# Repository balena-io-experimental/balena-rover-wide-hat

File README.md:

# Resin Rover Wide-HAT

This board is a full-fledged rover in a wide HAT form factor, which mean it covers an entire Raspberry Pi 3.

The motors are driven by two [DRV8830](www.ti.com/product/drv8830) I²C motor controllers, one for the left wheels and the other for the right wheels. The slave I²C address for the left wheels driver are ``0xC0h`` and ``0xC1h``, for write and read respectively. As for the right wheels driver, they are ``0xD0h`` and ``0xD1h``, respectively.

Currently the maximum current for each motor is 500mA.

The line following circuit is made from three reflective sensors, which are read by an [ADC](http://www.ti.com/product/ADS1015) at address ``0x48h``. The left, center and right sensors are read at analog inputs ``AIN0``, ``AIN1`` and ``AIN2`` respectively.

It supports a 2-cell LiPo battery with an on-board charger which should be supplied through a DC barrel jack connector from 9V to 12V, at 1A.

The only manufacturing constrain of this board is that it needs 2oz or higher copper weight.

Besides the components listed on the BoM, the rest of the parts needed are:

* 4 x Micro Metal Gearmotor ([example](https://shop.pimoroni.com/products/micro-metal-gearmotor-extended-back-shaft))
* 4 x Micro Metal Gearmotor Bracket ([example](https://shop.pimoroni.com/products/pimoroni-gearmotor-bracket-pair))
* 4 x Wheels ([example](https://shop.pimoroni.com/products/pololu-wheel-32x7mm-pair))
* 1 x 2-cell LiPo battery with JST-XH connector ([example](https://hobbyking.com/en_us/turnigy-5000mah-2s-20c-lipo-pack.html))

Raspberry Pi mounting holes were taken from [here](https://github.com/xesscorp/RPi_Hat.pretty/blob/master/RPi_Hat_Mounting_Hole.kicad_mod) and inductor footprint from [here](https://github.com/Tinkerforge/kicad-libraries/blob/master/SRN6045.kicad_mod).

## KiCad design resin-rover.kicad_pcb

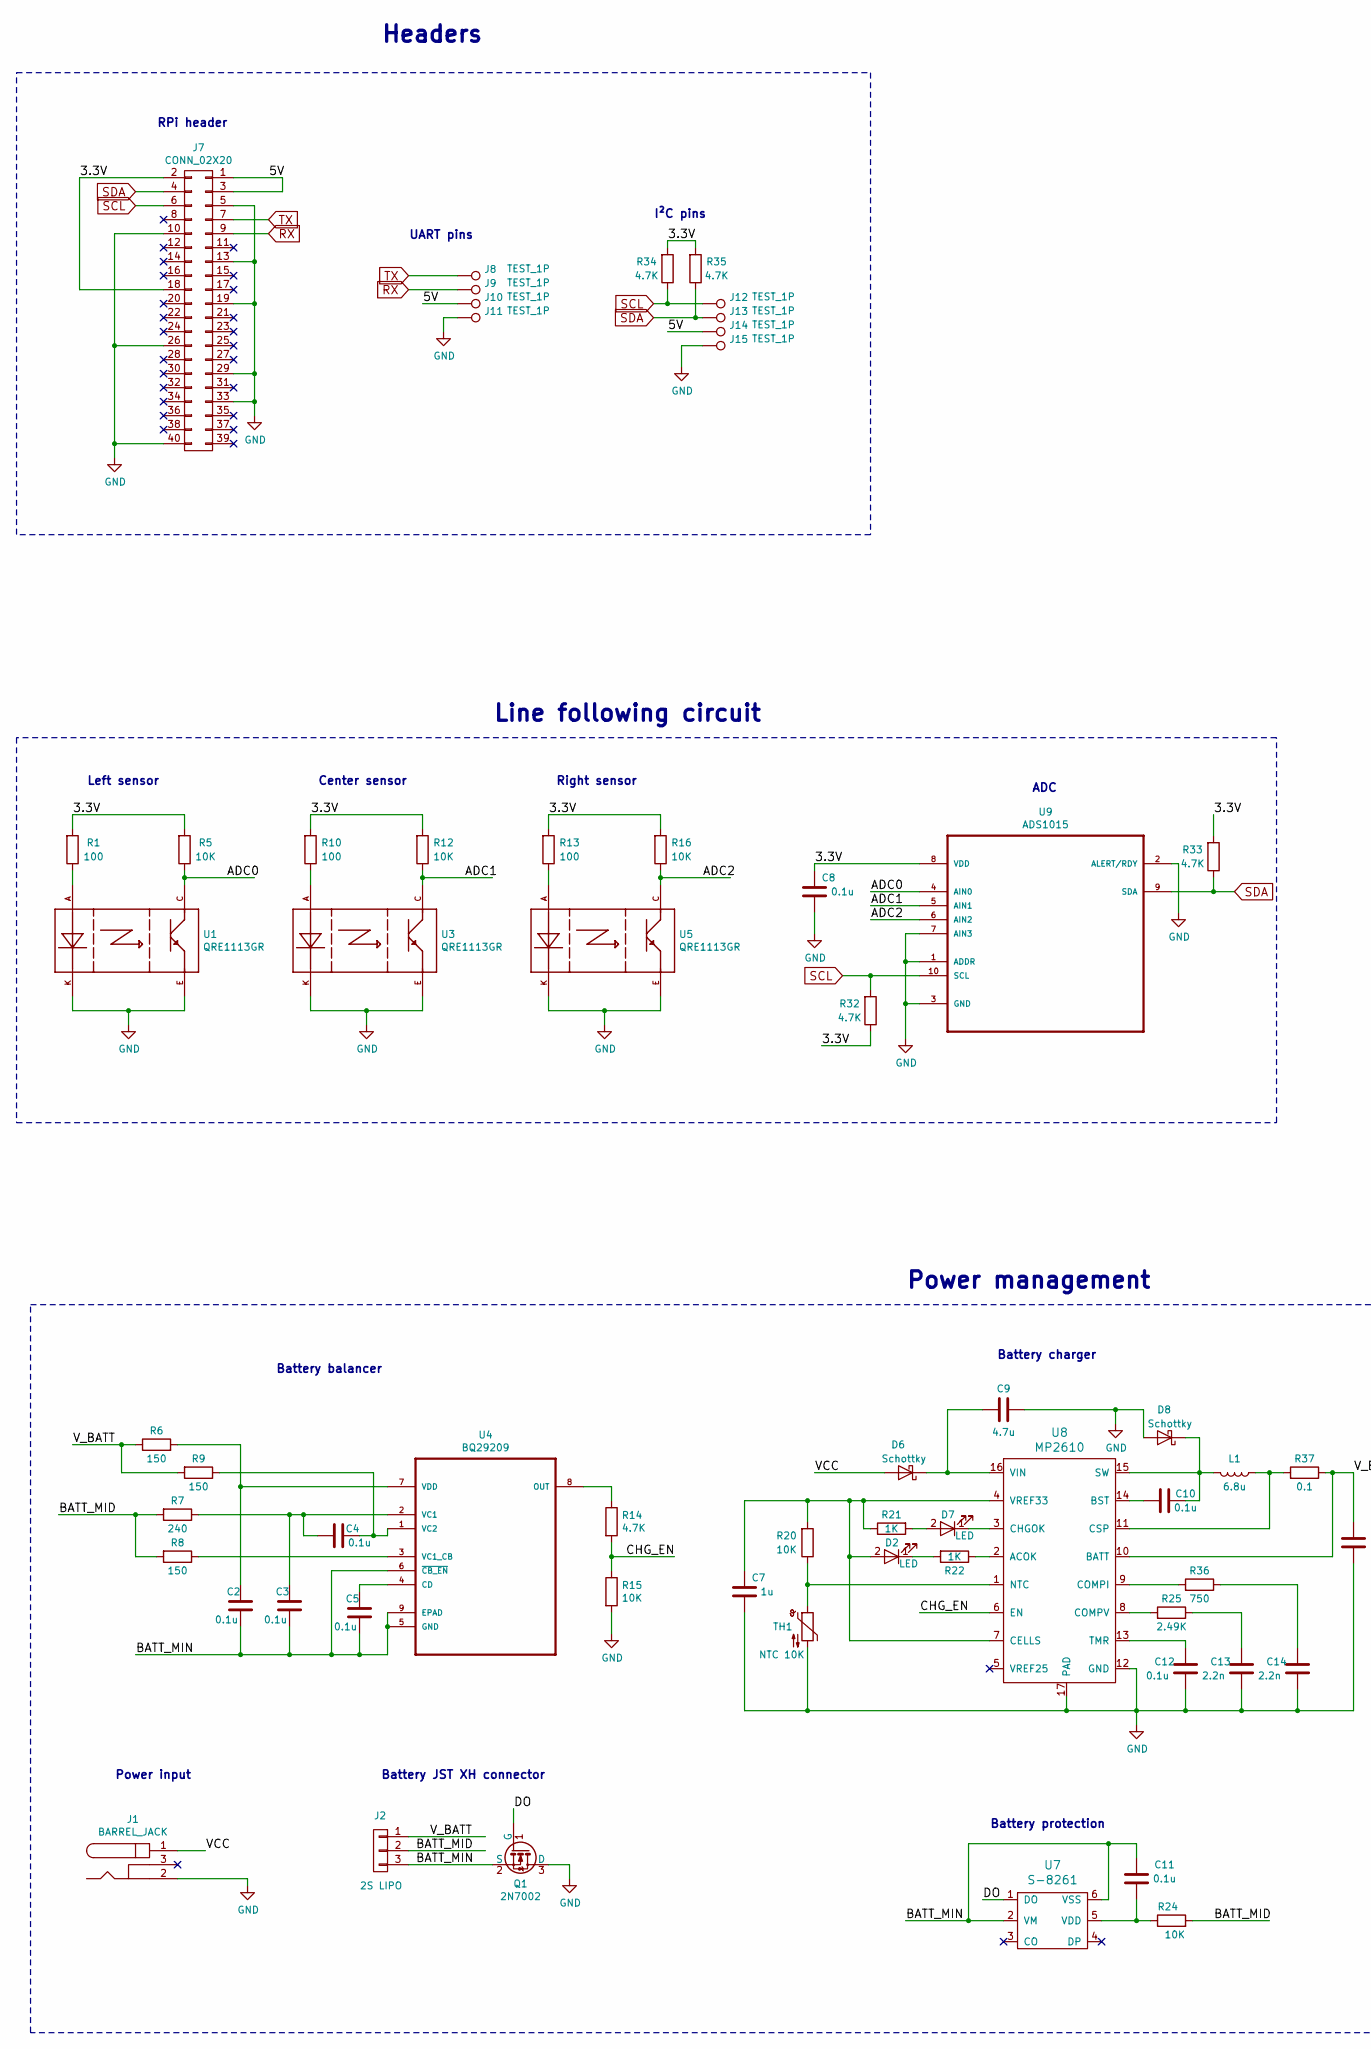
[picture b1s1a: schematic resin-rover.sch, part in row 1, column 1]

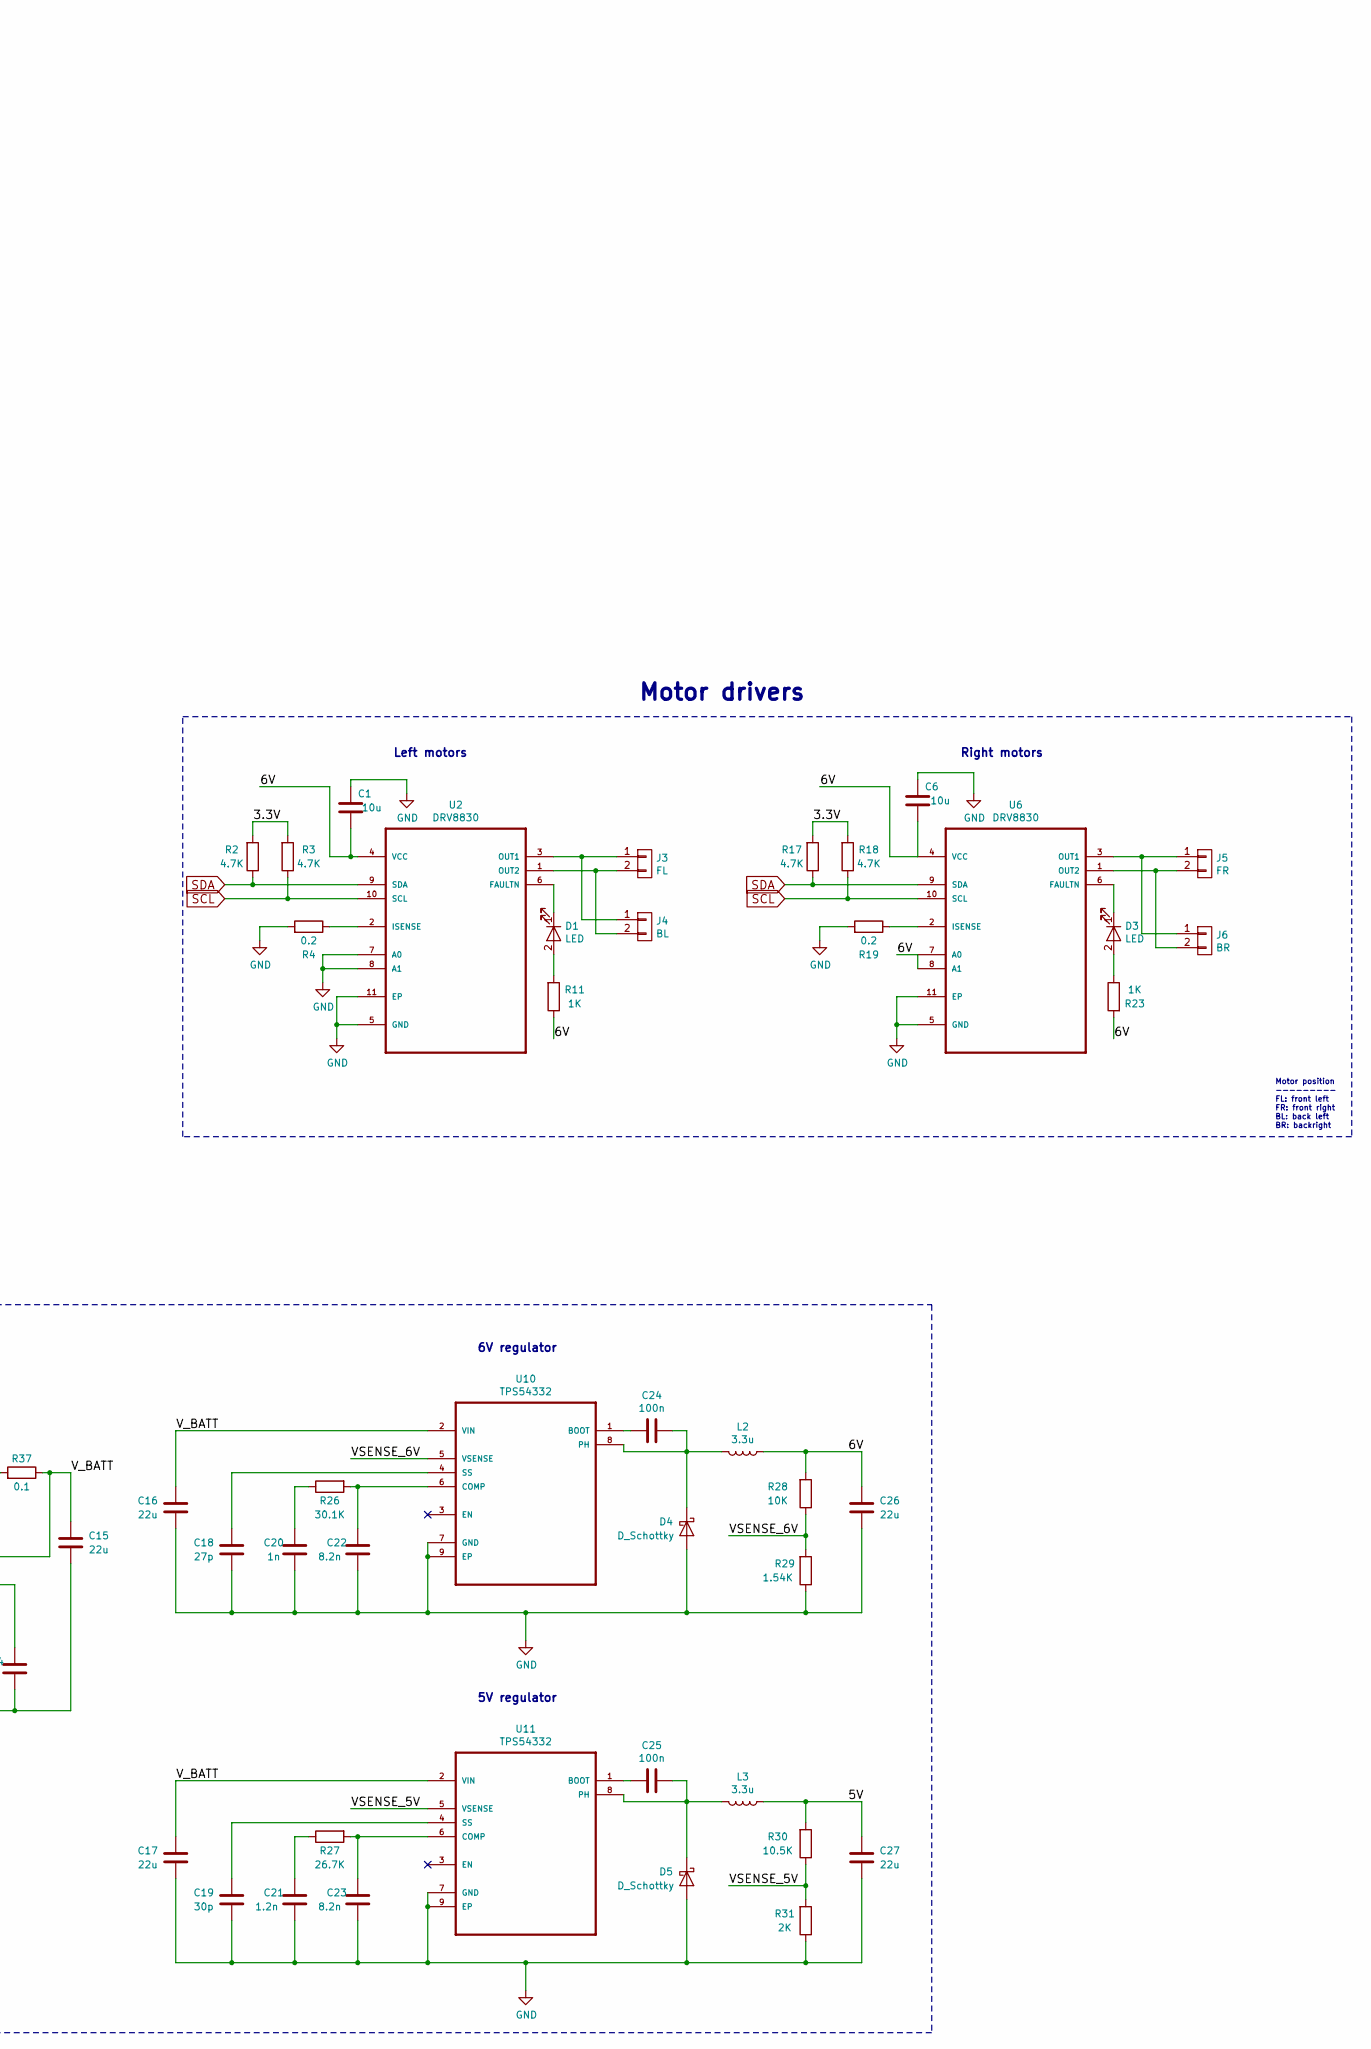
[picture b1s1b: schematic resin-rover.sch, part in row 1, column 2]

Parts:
C1, C6: 10u; C_0805
C2, C3, C4, C5, C8, C10, C11: 0.1u; C_0805
C7: 1u; C_0805
C9: 4.7u; C_0805
C12: 0.1u; C_0201
C13, C14: 2.2n; C_0201
C15, C26, C27: 22u; C_0603
C16, C17: 22u; C_1210
C18: 27p; C_0201
C19: 30p; C_0805
C20: 1n; C_0201
C21: 1.2n; C_0201
C22, C23: 8.2n; C_0201
C24, C25: 100n; C_0402
D1, D2, D3, D7: LED; LED_0603
D4: D_Schottky; D_SOD-123F
D5: D_Schottky; D_SMA_Standard
D6, D8: Schottky; D_SMA_Standard
J1: BARREL_JACK
J2: 2S LIPO; JST_XH_S03B-XH-A_03x2.50mm_Angled
J3: FL; PhoenixContact_MCV-G_02x3.81mm_Vertical
J4: BL; PhoenixContact_MCV-G_02x3.81mm_Vertical
J5: FR; PhoenixContact_MCV-G_02x3.81mm_Vertical
J6: BR; PhoenixContact_MCV-G_02x3.81mm_Vertical
J7: CONN_02X20; Pin_Header_Straight_2x20_Pitch2.54mm_SMD
J8, J9, J10, J11, J12, J13, J14, J15: TEST_1P; Measurement_Point_Round-SMD-Pad_Big
L1: 6.8u; SRN6045
L2, L3: 3.3u; SRN6045
Q1: 2N7002; SOT-23
R1, R10, R13: 100; R_0805
R2, R3, R14, R17, R18, R32, R33, R34, R35: 4.7K; R_0402
R4, R19: 0.2; R_0805
R5, R12, R15, R16, R20, R24, R28: 10K; R_0805
R6, R8, R9: 150; R_1206
R7: 240; R_1206
R11, R21, R22, R23: 1K; R_0402
R25: 2.49K; R_0603
R26: 30.1K; R_0402
R27: 26.7K; R_0402
R29: 1.54K; R_0805
R30: 10.5K; R_0805
R31: 2K; R_0805
R36: 750; R_0603
R37: 0.1; R_0805
TH1: NTC 10K; R_0603
U1, U3, U5: QRE1113GR; 4LEADSMD
U2, U6: DRV8830; SOP65P640X110-15N
U4: BQ29209; SON65P315X315X100-9N
U7: S-8261; SOT-23-6
U8: MP2610; QFN-16-1EP_4x4mm_Pitch0.65mm
U9: ADS1015; SOP50P490X110-10N
U10, U11: TPS54332; SOIC127P600X170-9N

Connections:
/3.3V: C8.2, J7.2, J7.18, R1.2, R2.2, R3.2, R5.2, R10.2, R12.2, R13.2, R16.2, R17.2, R18.2, R32.1, R33.2, R34.2, R35.2, U9.8 (VDD)
/5V: C27.2, J7.1, J7.3, J10.1, J14.1, L3.1, R30.2
/6V: C1.1, C6.1, C26.2, L2.1, R11.1, R23.2, R28.2, U2.4 (VCC), U6.4 (VCC), U6.7 (A0), U6.8 (A1)
/ADC0: R5.1, U1.C, U9.4 (AIN0)
/ADC1: R12.1, U3.C, U9.5 (AIN1)
/ADC2: R16.1, U5.C, U9.6 (AIN2)
/BATT_MID: J2.2, R7.2, R8.2, R24.2
/BATT_MIN: C2.2, C3.1, C5.2, C11.2, J2.3, Q1.2 (S), U4.5 (GND), U4.6 (~CB_EN), U4.9 (EPAD), U7.2 (VM), U7.6 (VSS)
/CHG_EN: R14.2, R15.1, U8.6 (EN)
/DO: Q1.1 (G), U7.1 (DO)
/VCC: D6.2 (A), J1.1
/VSENSE_5V: R30.1, R31.2, U11.5 (VSENSE)
/VSENSE_6V: R28.1, R29.2, U10.5 (VSENSE)
/V_BATT: C15.2, C16.2, C17.2, J2.1, R6.1, R9.2, R37.1, U8.10 (BATT), U10.2 (VIN), U11.2 (VIN)
GND: C1.2, C6.2, C7.1, C8.1, C9.2, C12.1, C13.1, C14.1, C15.1, C16.1, C17.1, C18.1, C19.1, C20.1, C21.1, C22.1, C23.1, C26.1, C27.1, D4.2 (A), D5.2 (A), D8.2 (A), J1.2, J7.5, J7.10, J7.13, J7.19, J7.26, J7.29, J7.33, J7.40, J11.1, J15.1, Q1.3 (D), R4.2, R15.2, R19.2, R29.1, R31.1, TH1.2, U1.E, U1.K, U2.5 (GND), U2.7 (A0), U2.8 (A1), U2.11 (EP), U3.E, U3.K, U5.E, U5.K, U6.5 (GND), U6.11 (EP), U8.12 (GND), U8.17 (PAD), U9.1 (ADDR), U9.2 (ALERT/RDY), U9.3 (GND), U9.7 (AIN3), U10.7 (GND), U10.9 (EP), U11.7 (GND), U11.9 (EP)
unnamed: C2.1, R6.2, U4.7 (VDD)
unnamed: C3.2, C4.2, R7.1, U4.2 (VC1)
unnamed: C4.1, R9.1, U4.1 (VC2)
unnamed: C5.1, U4.4 (CD)
unnamed: C7.2, D2.2 (A), R20.2, R21.1, U8.4 (VREF33), U8.7 (CELLS)
unnamed: C9.1, D6.1 (K), U8.16 (VIN)
unnamed: C10.1, D8.1 (K), L1.2, U8.15 (SW)
unnamed: C10.2, U8.14 (BST)
unnamed: C11.1, R24.1, U7.5 (VDD)
unnamed: C12.2, U8.13 (TMR)
unnamed: C13.2, R25.1
unnamed: C14.2, R36.1
unnamed: C18.2, U10.4 (SS)
unnamed: C19.2, U11.4 (SS)
unnamed: C20.2, R26.1
unnamed: C21.2, R27.1
unnamed: C22.2, R26.2, U10.6 (COMP)
unnamed: C23.2, R27.2, U11.6 (COMP)
unnamed: C24.1, D4.1 (K), L2.2, U10.8 (PH)
unnamed: C24.2, U10.1 (BOOT)
unnamed: C25.1, D5.1 (K), L3.2, U11.8 (PH)
unnamed: C25.2, U11.1 (BOOT)
unnamed: D1.1 (K), U2.6 (FAULTN)
unnamed: D1.2 (A), R11.2
unnamed: D2.1 (K), R22.2
unnamed: D3.1 (K), U6.6 (FAULTN)
unnamed: D3.2 (A), R23.1
unnamed: D7.1 (K), U8.3 (CHGOK)
unnamed: D7.2 (A), R21.2
unnamed: J3.1, J4.1, U2.3 (OUT1)
unnamed: J3.2, J4.2, U2.1 (OUT2)
unnamed: J5.1, J6.1, U6.3 (OUT1)
unnamed: J5.2, J6.2, U6.1 (OUT2)
unnamed: L1.1, R37.2, U8.11 (CSP)
unnamed: R1.1, U1.A
unnamed: R4.1, U2.2 (ISENSE)
unnamed: R8.1, U4.3 (VC1_CB)
unnamed: R10.1, U3.A
unnamed: R13.1, U5.A
unnamed: R14.1, U4.8 (OUT)
unnamed: R19.1, U6.2 (ISENSE)
unnamed: R20.1, TH1.1, U8.1 (NTC)
unnamed: R22.1, U8.2 (ACOK)
unnamed: R25.2, U8.8 (COMPV)
unnamed: R36.2, U8.9 (COMPI)
RX: J7.9, J9.1
SCL: J7.6, J12.1, R3.1, R18.1, R32.2, R34.1, U2.10 (SCL), U6.10 (SCL), U9.10 (SCL)
SDA: J7.4, J13.1, R2.1, R17.1, R33.1, R35.1, U2.9 (SDA), U6.9 (SDA), U9.9 (SDA)
TX: J7.7, J8.1

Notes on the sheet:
Power input
Battery protection
Battery balancer
Battery JST XH connector
Battery charger
Power management
Motor drivers
Left motors
Right motors
Motor position --------- FL: front left FR: front right BL: back left BR: backright
6V regulator
5V regulator
UART pins
RPi header
I²C pins
Line following circuit
Center sensor
Left sensor
Right sensor
ADC
Headers

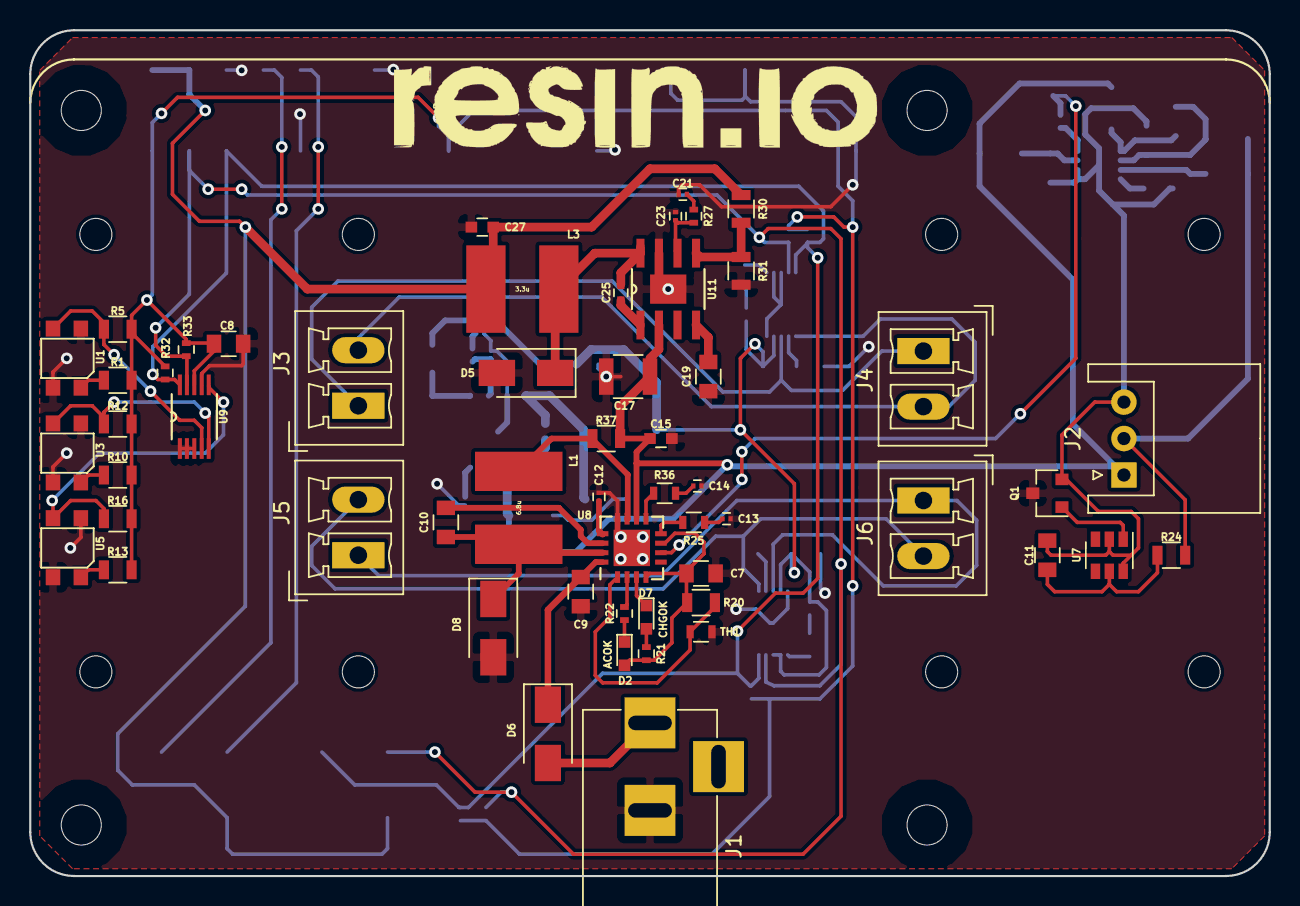
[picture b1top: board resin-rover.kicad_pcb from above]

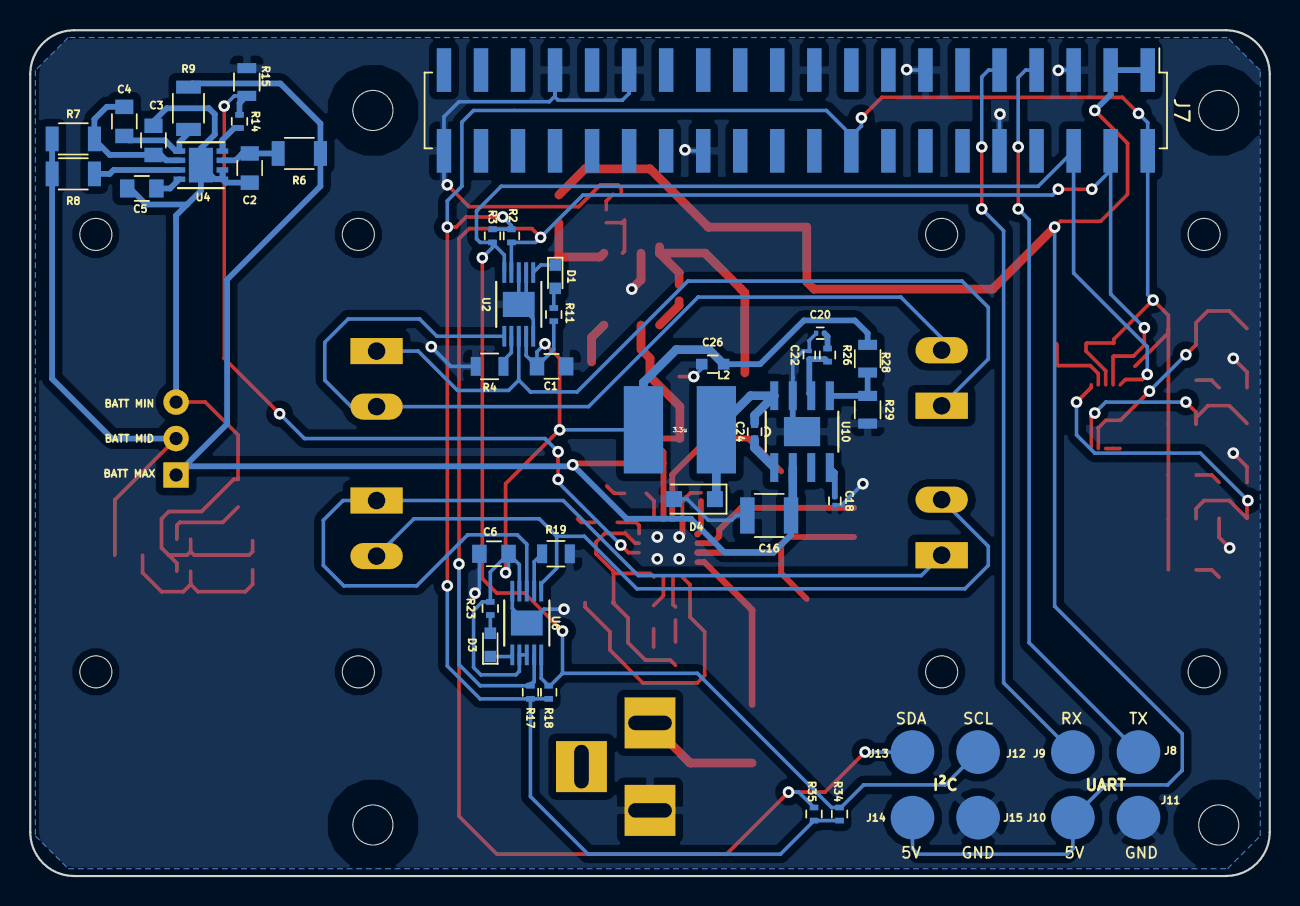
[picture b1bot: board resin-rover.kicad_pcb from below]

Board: 2 copper layers, 85.0 x 58.0 mm, 103 parts (48 on the bottom side), 64 nets.

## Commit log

2017-04-10 Add 5V and 6V voltage regulators
2017-04-10 Add line following circuit
2017-04-11 Add BOM and change battery charger to MP2610
2017-04-12 Add layout and fabrication files
2017-06-08 Update README and repo cleanup
